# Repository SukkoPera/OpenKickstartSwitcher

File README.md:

# OpenKickstartSwitcher
OpenKickstartSwitcher is an Open Hardware Kickstart Switcher for Amiga Computers.

### Summary
OpenKickstartSwitcher is a Kickstart switcher for Amiga computers, based on [work by Henryk Richter](http://bax.comlab.uni-rostock.de/en/hardware/amiga500/kickstart-eprom/). It allows switching among three or six different Kickstart images, stored in an EPROM. The switching can be done through physical switches or by pressing the mouse/joystick buttons at power-up. The latter requires [an external add-on board](https://github.com/SukkoPera/OpenAmigaMouseTrigger) that is another project of mine.

### Compatibility
The adapter is mostly targeted at Amiga 500+ users, who can use it to switch among Kickstart 3.1 (or 2.04 if they want to keep the version that came originally on their machines), 1.3 and maybe [a diagnostic ROM](http://www.diagrom.com), improving compatibility with older software that does not work correctly on Kickstart 2.x. Note that the adapter will have a tight fit on Rev.8A.1 mainboards (which is what 500+'s have): V2 was reworked to fix this issue, but the upper part of the shield will still touch the EPROM, so it is recommended to apply some insulation tape on the contact point or to remove the upper shield altogether (this won't do any harm, so don't worry too much about it, it will actually improve the internal cooling).

The situation is pretty much the same on Amiga 500s with Rev.6A mainboards.

Amiga 500 Rev.3 and 5 mainboards have their Kickstart sockets placed further towards the back of the machine, which allows the adapter to fit much better. There is plenty is space and you should manage to put everything in place and close the case properly. 

Besides the 500/500+, OpenKickstartSwitcher will work correctly on all Amiga models that have a single-chip Kickstart: this means it can be used on the A2000 just as well. It will also work on the A600, but you won't be able to place the keyboard back into the case, so it might be more useful when troubleshooting a broken mainboard. The same applies for the CDTV, but [a special version](https://github.com/SukkoPera/OpenKickstartSwitcherCDTV) was designed for this model, which will fit perfectly.

In all cases, **pay attention to put the revision selection jumper in the correct position**: one position is for A500 Rev.3 and 5, the other one is for all other cases, including A600 and A2000.

### Assembly
Solder all components to the board. No particular order is recommended, but starting with the smaller components might be a good idea.

The value of the two single resistors is not critical, 10k is recommended, but probably any value between 5k and 50k will do. If you intend on using 27C160 / 29F1615 with six images, you will need a pullup resistor of the same value between A19 and VCC; an 0805 SMD resistor fits in that space just fine. This is a tiny part, but it can be soldered without a loupe or microscope since the pads are pretty big.

My tests show that an SN74HC00 gate works fine. I don't recommend using parts from the *HC* series though, *HCT* or *LS* should be preferred.

The two resistor arrays are not always needed. First of all, these will end up in parallel to RP106 and RP107 on A500 boards, so you must skip them if those are already populated on your particular board. If they are not, you might still get away without them, depending on the particular EPROM you are using: I have several EPROMs of the same model (but different production batches), and some need the resistors while others don't, so the only way to find out is actual testing. For this I usually just load a Kickstart 1.2 disk, start up the four *Demos* and leave them running for a while. If the system does not hang/crash in like 15 minutes (usually it is much quicker than that, sometimes it even hangs before you can start all the demos!), you don't need them, otherwise you do. If you decide to install them, they must be of the *bussed* type and the recommended value is 4.7k. Be aware that these parts are polarized and must be installed in a certain verse!

### EPROM Selection and Switch Wiring
Since V2, the adapter can be used with either 27C800 or 27C160 EPROMs (earlier versions only supported the former). I recommend using *-100F1* EPROMs by ST, but access time is not critical: use 100ns or faster EPROMs if you can, but anything up to 150ns should work reliably. If you do not have a UV eraser, you may use an MX29F1615 DIP42 chip which is a direct, pin compatible replacement of 27C160.

#### 27C800
With a 27C800 EPROM, the adapter supports 2x256 KB Kickstart images (i.e.: up to version 1.3) and 1x512 KB image (version 2 and later).

To switch between ROMs, you will need two SPDT switches, connected to the SW1/SW2 pads and ground. A ground pad is available on the board, but any ground spot on the mainboard can be used as well, if easier to reach.

| ROM Image # | Size (KB) | SW1 | SW2 |
|-------------|-----------|-----|-----|
| 1           | 256       | LOW | LOW |
| 2           | 256       | HIGH| LOW |
| 3           | 512       |  x  | HIGH|

(x = Don't Care)

So, basically:
* If SW2 is HIGH, the 512 KB Kickstart image is selected, regardless of SW1.
* If SW2 is LOW, SW1 controls which one of the two 256 KB images is enabled: LOW selects the first one, and HIGH selects the second one.

You can also use a single ON-OFF-ON DPDT switch, just wire ground to the middle pins, SW1 and SW2 on one side and SW2 on the other.

As SW1/SW2 will both read as HIGH if left unconnected, the 512 KB Kickstart will be selected if no switches are wired.

You can fully ignore the A19 pad on the bottom side of the board, when using a 27C800 EPROM.

#### 27C160 / 29F1615
With a 27C160 EPROM, the adapter supports up to 4x256 KB Kickstart images and 2x512 KB images.

You will need to solder an additional switch to the A19 pad on the bottom side of the board. VCC and GND pads are provided nearby so that you can also solder a pull-up/down resistor.

If you want to keep using a single switch, an eight position BCD coded rotary switch is an option. In your BCD switch's documentation, pins are going to be called 1, 2, 4, and C (collect). Wire collect to GND, SW1 to pin called 1, SW2 to pin 2, and A19 to pin 4; remember about the pullup resistor between A19 and VCC! This will result in a switch that goes "backwards": first image from your EPROM will be on switch position number 7. 512k images take two switch positions (0-1 and 4-5).

| ROM Image # | Size (KB) | SW1 | SW2 | A19 |
|-------------|-----------|-----|-----|-----|
| 1           | 256       | LOW | LOW | LOW |
| 2           | 256       | HIGH| LOW | LOW |
| 3           | 512       |  x  | HIGH| LOW |
| 4           | 256       | LOW | LOW | HIGH|
| 5           | 256       | HIGH| LOW | HIGH|
| 6           | 512       |  x  | HIGH| HIGH|

**IMPORTANT: ALWAYS TURN YOUR AMIGA OFF BEFORE MOVING THE SELECTION SWITCHES!**

#### Flashing Notes
When flashing the EPROM, make sure that the ROM images you are using are exactly 262144 or 524288 bytes long, and just concatenate them. Take care to use the correct byte ordering, as the Amiga hardware expects 16-bit words to be stored in the *big-endian* format (which is NOT the format UAE expects them in, for the record). On Unix-like systems you can use the *conv=swab* option of *dd* to change the byte ordering.

27C800s and 27C160 are 42-pin EPROMs and most programmers only support chips up to 40 pins. This is the case with [the popular TL866 programmer](http://autoelectric.cn/EN/TL866_main.html), for instance. You can get around this limitation with an adapter PCB. There are at least two open designs of such an adapter:
* [One by keirff](https://github.com/keirf/PCB-Projects) (who, interestingly, has his own Kickstart Switcher)
* [And another one by gaggi](https://github.com/gaggi/27c160-tl866-adapter)

I have only used the latter and found it to be working fine. 

The above adapters *should* work with MX29F1615, but this has not been confirmed; the official ADP_D42_EX-A for the T48 programmer is confirmed working with them.

### Installation
Once your OpenKickstartSwitcher is assembled and programmed, the rest of the installation should be pretty straightforward:
* Open your Amiga.
* Remove the shielding.
* Set the revision selection jumper on OpenKickstartSwitcher according to the Amiga model (see above). On Amiga 500/500+'s you can identify the mainboard revision by looking at the bottom right corner near the floppy drive zone.
* Identify the Kickstart chip.
* Carefully remove it.
* Plug OpenKickstartSwitcher in its place, making sure to match the correct orientation.
* Drill two holes into the back of your Amiga (or wherever you prefer) and screw two switches in there.
* Solder wires to switches.
* Replace your shielding.
* Close your Amiga.

Of course, if you use OpenAmigaMouseTrigger there is no need to drill any holes.

### DiagROM
The excellent [DiagROM by chucky](http://www.diagrom.com) can be used with OpenKickstartSwitcher.

Normally it is distributed as a 512 KB image, but most of the space is unused, so I have created a 256 KB version of DiagROM 1.0 by simply truncating the image. It is **NOT GUARANTEED TO WORK**, but it looks fine to me. It can be [downloaded here](https://github.com/SukkoPera/OpenKickstartSwitcher/files/1777856/diagrom-256k.zip).

### License
OpenKickstartSwitcher is Open Hardware. If you make any modifications to the board, please contribute them back.

### Support the Project
Since the project is open you are free to get the PCBs made by your preferred manufacturer, however in case you want to support the development, you can order them from PCBWay through this link:

You get cheap, professionally-made and good quality PCBs, I get some credit that will help with this and [other projects](https://www.pcbway.com/project/member/shareproject/?bmbid=41100). You won't even have to worry about the various PCB options, it's all pre-configured for you!

Also, if you still have to register to that site, [you can use this link](https://www.pcbway.com/setinvite.aspx?inviteid=41100) to get some bonus initial credit (and yield me some more).

Again, if you want to use another manufacturer, feel free to, don't feel obligated :). But then you can buy me a coffee if you want:

### Thanks
Thanks to Henryk Richter and the guys at the Italian Amiga Page forum.
Kudos to Aldo PRS for prividing information about how the adapter fits on the various A500/500+ mainboard revisions.

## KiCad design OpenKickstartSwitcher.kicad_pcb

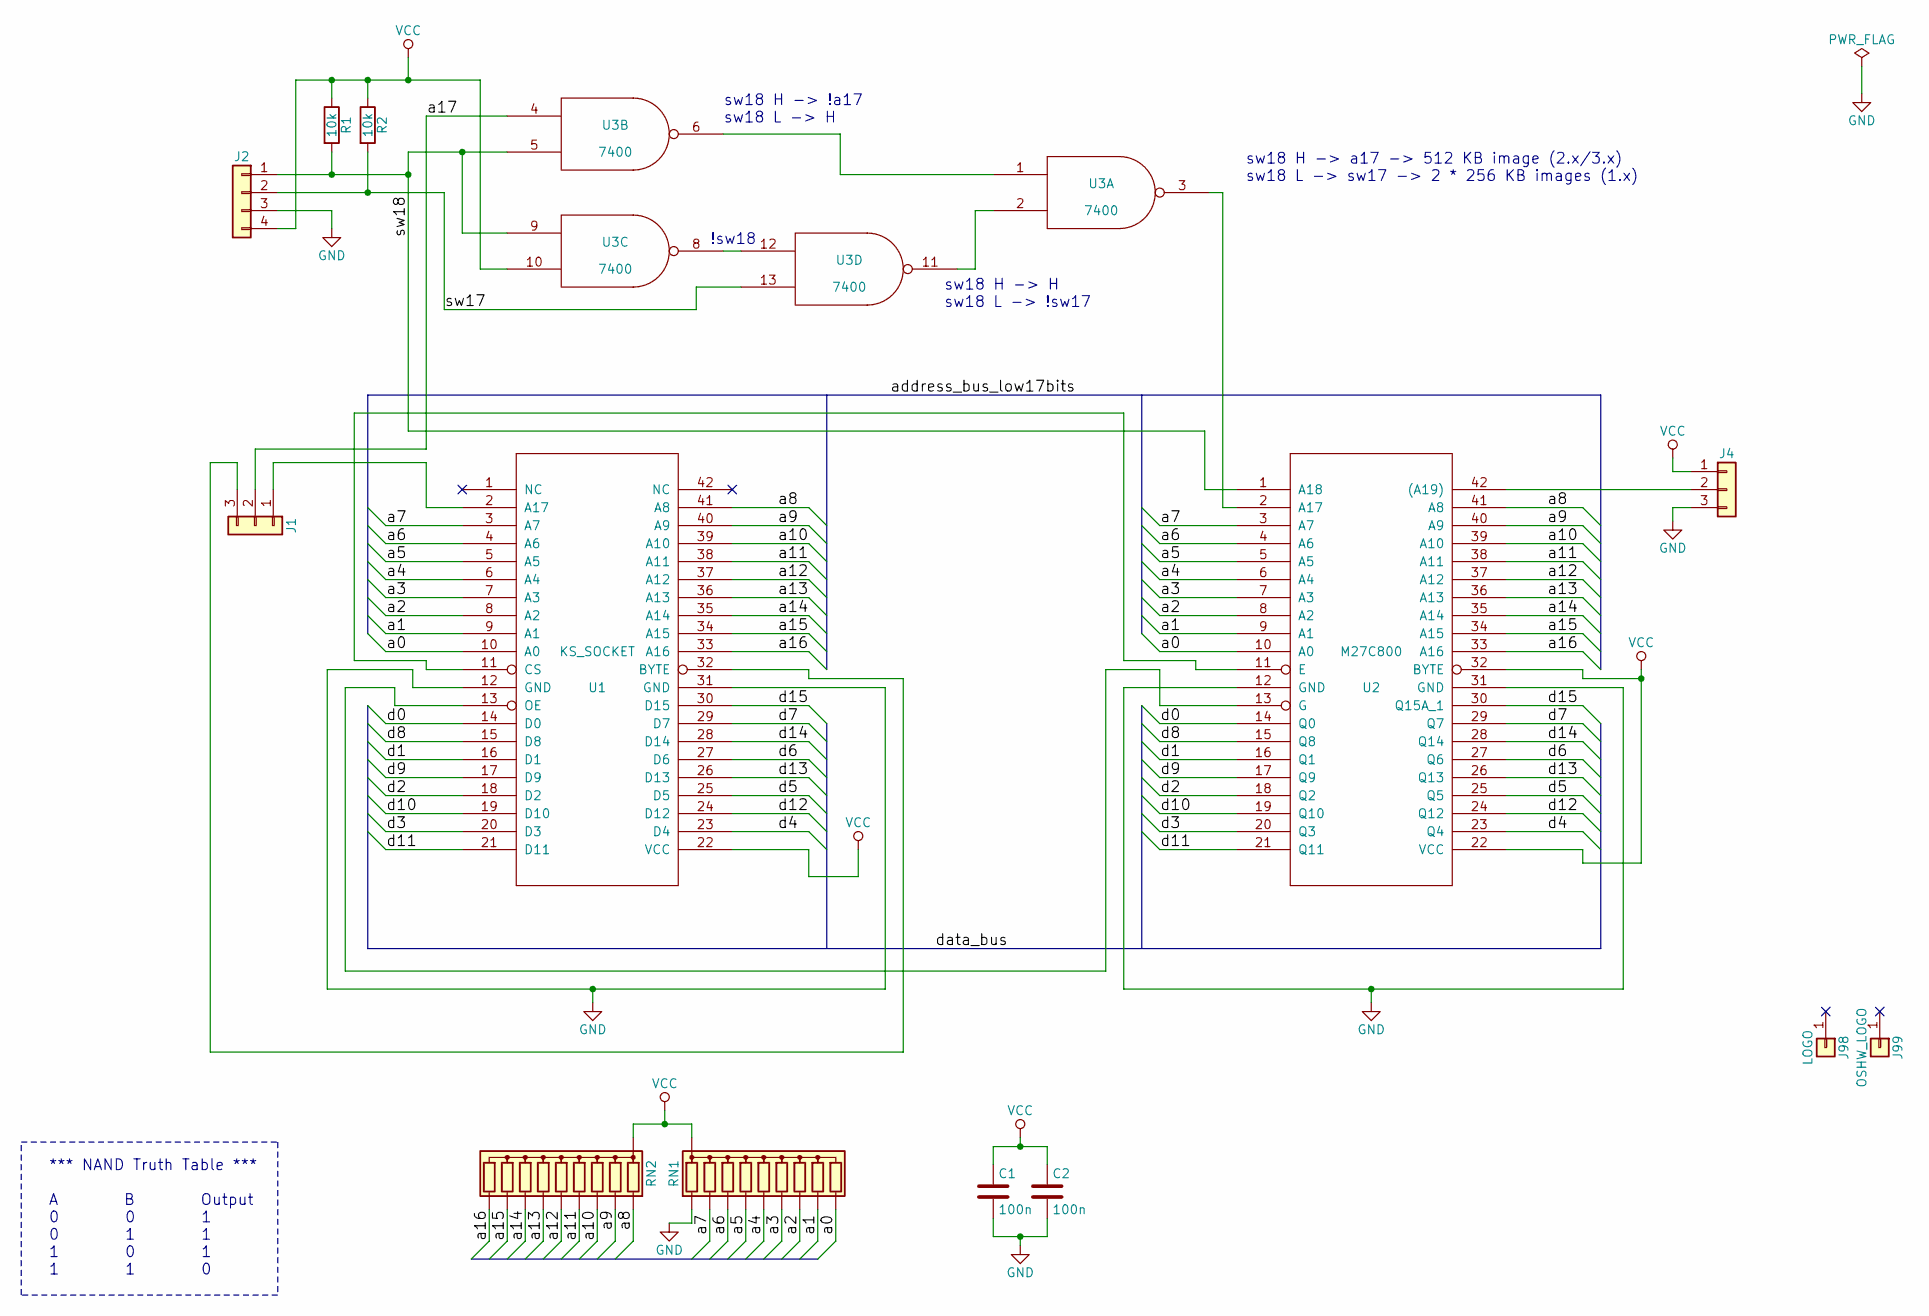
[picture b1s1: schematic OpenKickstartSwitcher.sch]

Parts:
C1, C2: 100n; C_Disc_D7.0mm_W2.5mm_P5.00mm
J1: Conn_01x03; Pin_Header_Straight_1x03-ModSilkS
J2: Conn_01x04; Solderable_PinHeader_1x04
J4: Conn_01x03; SolderJumper
J98: LOGO; logo
J99: OSHW_LOGO; Logo_copper_OSHW_6x6mm
R1, R2: 10k; R_Axial_DIN0204_L3.6mm_D1.6mm_P7.62mm_Horizontal
RN1, RN2: 4.7k; R_Array_SIP10
U1: KS_SOCKET; DIP-42_DualHeaderStrips
U2: M27C800; DIP-42_Socket
U3: 7400; DIP-14_W7.62mm_Socket

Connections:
/a0: RN1.10 (R9), U1.10 (A0), U2.10 (A0)
/a1: RN1.9 (R8), U1.9 (A1), U2.9 (A1)
/a2: RN1.8 (R7), U1.8 (A2), U2.8 (A2)
/a3: RN1.7 (R6), U1.7 (A3), U2.7 (A3)
/a4: RN1.6 (R5), U1.6 (A4), U2.6 (A4)
/a5: RN1.5 (R4), U1.5 (A5), U2.5 (A5)
/a6: RN1.4 (R3), U1.4 (A6), U2.4 (A6)
/a7: RN1.3 (R2), U1.3 (A7), U2.3 (A7)
/a8: RN2.2 (R1), U1.41 (A8), U2.41 (A8)
/a9: RN2.3 (R2), U1.40 (A9), U2.40 (A9)
/a10: RN2.4 (R3), U1.39 (A10), U2.39 (A10)
/a11: RN2.5 (R4), U1.38 (A11), U2.38 (A11)
/a12: RN2.6 (R5), U1.37 (A12), U2.37 (A12)
/a13: RN2.7 (R6), U1.36 (A13), U2.36 (A13)
/a14: RN2.8 (R7), U1.35 (A14), U2.35 (A14)
/a15: RN2.9 (R8), U1.34 (A15), U2.34 (A15)
/a16: RN2.10 (R9), U1.33 (A16), U2.33 (A16)
/a17: J1.2, U3.4
/d0: U1.14 (D0), U2.14 (Q0)
/d1: U1.16 (D1), U2.16 (Q1)
/d2: U1.18 (D2), U2.18 (Q2)
/d3: U1.20 (D3), U2.20 (Q3)
/d4: U1.23 (D4), U2.23 (Q4)
/d5: U1.25 (D5), U2.25 (Q5)
/d6: U1.27 (D6), U2.27 (Q6)
/d7: U1.29 (D7), U2.29 (Q7)
/d8: U1.15 (D8), U2.15 (Q8)
/d9: U1.17 (D9), U2.17 (Q9)
/d10: U1.19 (D10), U2.19 (Q10)
/d11: U1.21 (D11), U2.21 (Q11)
/d12: U1.24 (D12), U2.24 (Q12)
/d13: U1.26 (D13), U2.26 (Q13)
/d14: U1.28 (D14), U2.28 (Q14)
/d15: U1.30 (D15), U2.30 (Q15A_1)
/sw17: J2.2, R2.2, U3.13
/sw18: J2.1, R1.2, U2.1 (A18), U3.5, U3.9
GND: C1.2, C2.2, J2.3, J4.3, RN1.2 (R1), U1.12 (GND), U1.31 (GND), U2.12 (GND), U2.31 (GND), U3.7 (GND)
unnamed: J1.1, U1.2 (A17)
unnamed: J1.3, U1.32 (BYTE)
unnamed: J4.2, U2.42 ((A19))
unnamed: U1.11 (CS), U2.11 (E)
unnamed: U1.13 (OE), U2.13 (G)
unnamed: U2.2 (A17), U3.3
unnamed: U3.1, U3.6
unnamed: U3.2, U3.11
unnamed: U3.8, U3.12
VCC: C1.1, C2.1, J2.4, J4.1, R1.1, R2.1, RN1.1 (common), RN2.1 (common), U1.22 (VCC), U2.22 (VCC), U2.32 (BYTE), U3.10, U3.14 (VCC)

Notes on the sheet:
sw18 H -> a17 -> 512 KB image (2.x/3.x) sw18 L -> sw17 -> 2 * 256 KB images (1.x)
!sw18
sw18 H -> !a17 sw18 L -> H
sw18 H -> H sw18 L -> !sw17
*** NAND Truth Table *** A B Output 0 0 1 0 1 1 1 0 1 1 1 0

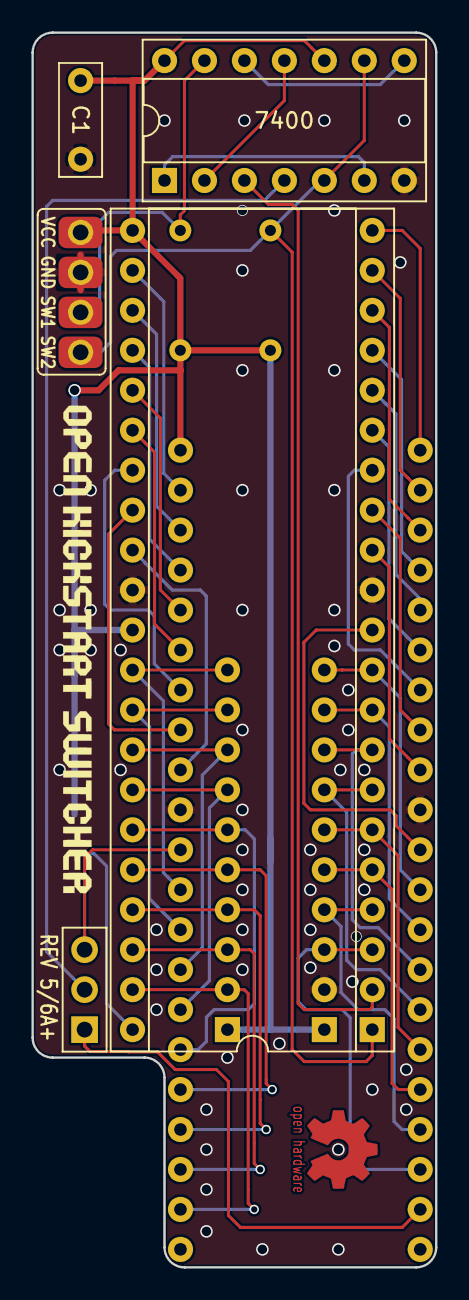
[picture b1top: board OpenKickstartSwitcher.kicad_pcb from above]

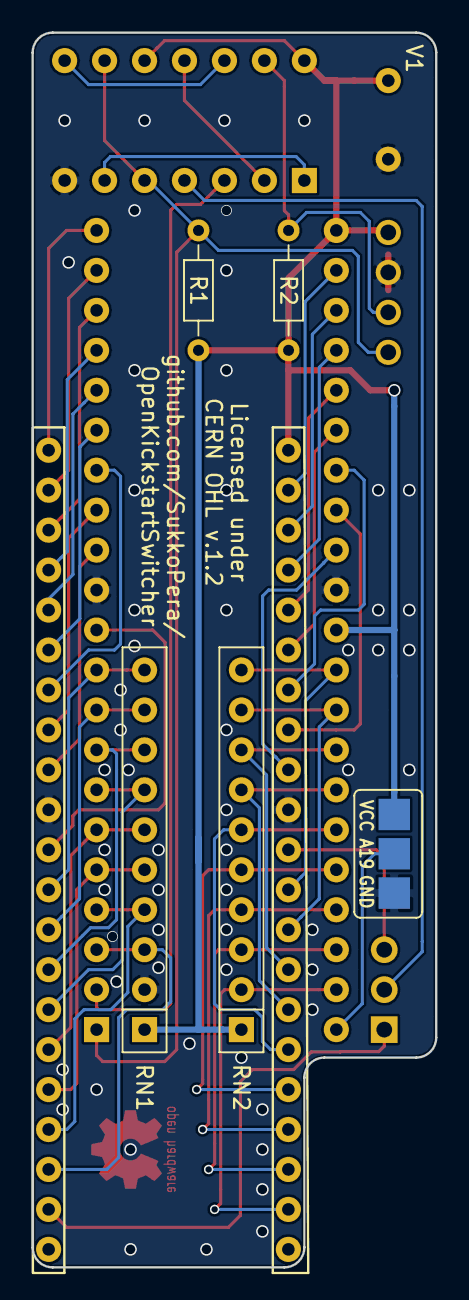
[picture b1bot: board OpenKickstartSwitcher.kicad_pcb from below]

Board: 2 copper layers, 25.7 x 78.5 mm, 13 parts (5 on the bottom side), 47 nets.

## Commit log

2017-12-15 Fix EPROM footprint
2017-12-15 Add OSHW logo and URL
2017-12-15 Move logo/URL slightly
2017-12-15 Slight corner fixes
2017-12-15 Added capacitor, more space for resistors and minor adjustments
2017-12-17 Add capacitor on 7400 I don't like this too much, tracks under the 7400 are pretty messy. Let's see if we can come up with something better.
2017-12-18 Much better now :)
2017-12-18 Re-add OSHW logo
2017-12-18 Minor routing adjustments
2017-12-22 Add logo and improve ground stitching
2018-01-07 Final touches for V1
2018-01-07 Add README
2018-01-07 Add note on programmers
2018-02-02 Tentative schematics for 5-kickstart version PCB NOT YET UPDATED
2018-02-02 Update schematics PDF
2018-02-02 Update schematics
2018-04-10 Fix form factor for a better fit in A500's
2018-04-10 Almost ready for V2
2018-04-10 Minor fixes
2018-04-10 Make logo larger
2018-04-10 Use smaller footprint for resistors
2018-04-12 Routing improvements
2018-04-12 Replace SW3 with a solder jumper
2018-04-20 Minor adjustments
2018-06-24 Update renders and schematics PDF
2018-06-24 Erm ^_^
2018-12-14 Initial commit of CDTV version - NOT READY YET
2018-12-14 Work in progress
2018-12-21 Almost there...
2018-12-22 Almost there... (again)
2018-12-22 Ready for V1-cdtv!
2018-12-22 Slightly move version marker
2019-08-29 Update model/revision fitting information
    Thanks Aldo!
2019-08-29 Use flashing info rom OpenKickstartSwitcherCDTV
2019-08-29 Erm ^___^
2019-08-29 Add coffee
2019-08-29 Remove all mentions of "triple"
2019-08-29 Fix typo
2025-02-02 Added info about MX29F1615 and BCD switches
    Addresses #6
2026-02-13 Update coffee donation link image in README
    Updated the 'Buy Me a Coffee' link to a new image source.
2026-02-13 Remove 'Get Help' section from README
    Removed the 'Get Help' section from the README.

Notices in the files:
OpenKickstartSwitcher.kicad_pcb:
Licensed under
CERN OHL v.1.2
